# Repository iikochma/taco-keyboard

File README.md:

# Taco Keyboard

A highly ergonomic custom mechanical keyboard designed using KiCad, QMK, and Shapr3D.

The keyboard uses a single-piece design with approximately 60° tenting, integrated pointing devices for both hands, and a highly optimized keymap inspired by the Hands Down layout and Ben Vallack's 18-key keyboard concepts.

## Key Features

- 29-key custom layout ("30% keyboard")

- Approximately 60° tenting and aggressive inward rotation

- Dual integrated trackpads

- Custom reversible PCB designed in KiCad

- Custom QMK firmware

- Custom 3D-printed enclosure designed in Shapr3D

## Design Goals

The project was created to explore extreme ergonomic keyboard design while maintaining high typing efficiency.

The keymap is heavily inspired by the Hands Down layout and Ben Vallack's 18-key workflow. While the keyboard contains 29 keys, the majority of daily typing is performed using approximately 20 keys combined with layers and modifiers.

The layout was further optimized for LaTeX-heavy workflows, reducing hand movement for frequently used symbols and commands.

## Hardware

A single reversible PCB design is used for both sides of the keyboard, reducing manufacturing complexity and cost.

## Repository Structure

- `cad/` - Shapr3D, STEP, and STL files

- `firmware/` - QMK firmware

- `images/` - Photos and renders

- `pcb/` - KiCad project files

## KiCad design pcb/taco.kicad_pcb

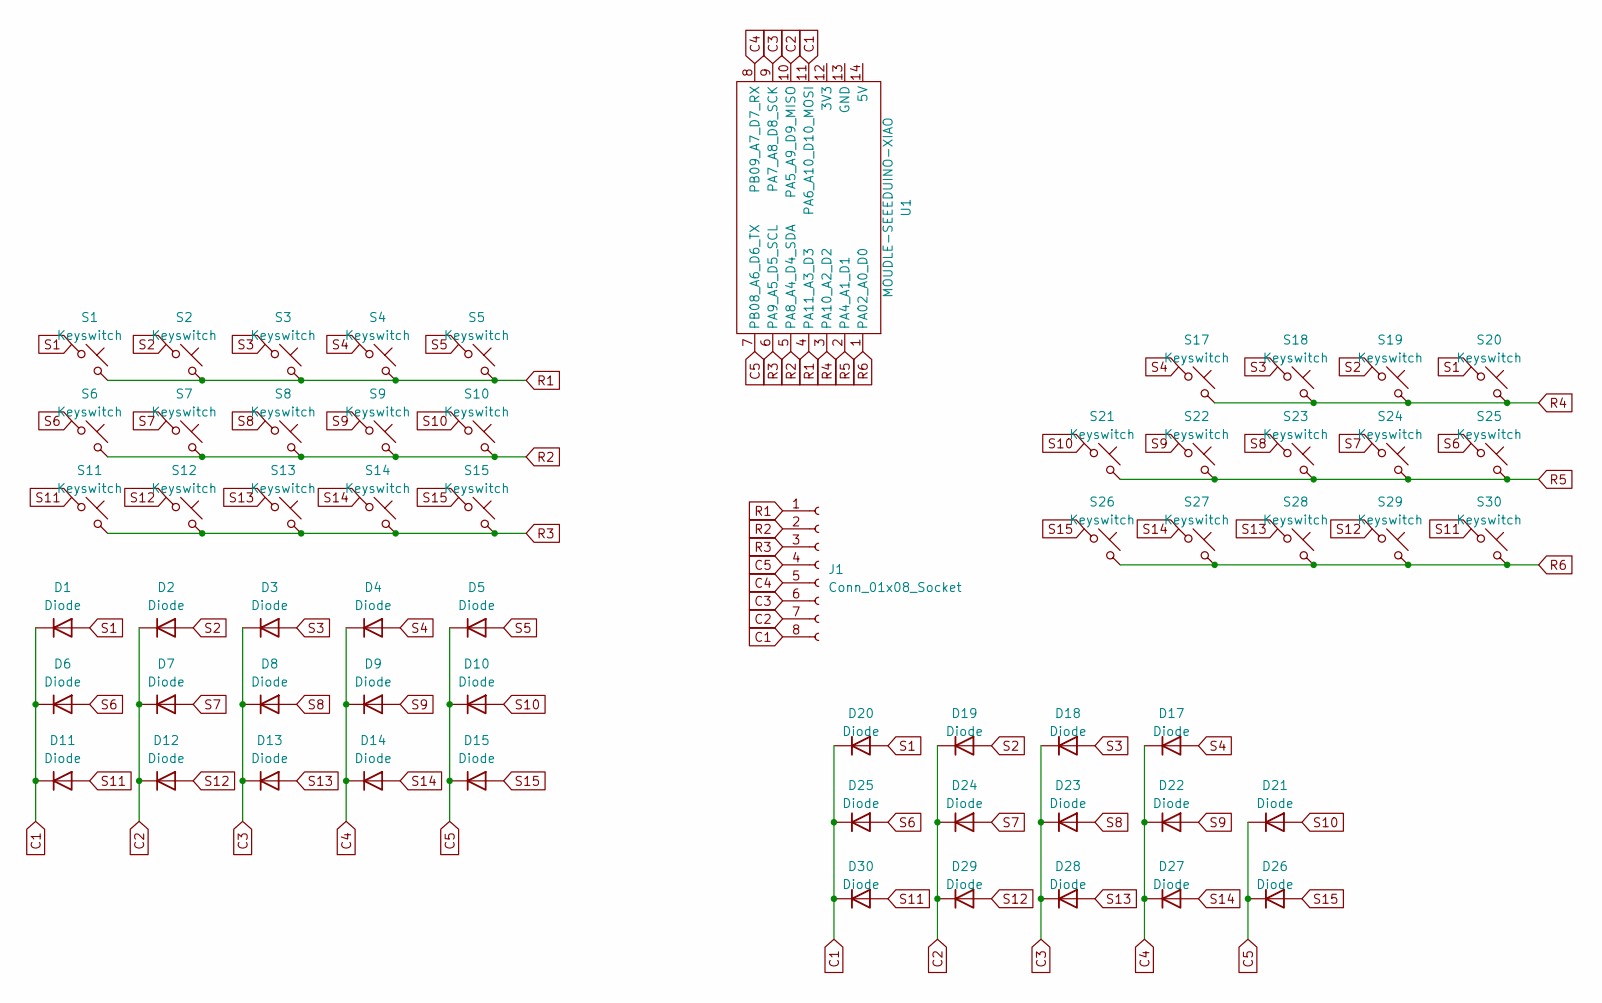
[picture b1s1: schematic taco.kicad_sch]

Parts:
D1, D2, D3, D4, D5, D6, D7, D8, D9, D10, D11, D12, D13, D14, D15, D17, D18, D19, D20, D21, D22, D23, D24, D25, D26, D27, D28, D29, D30: Diode; Diode_DO-35
J1: Conn_01x08_Socket; PinSocket_1x08_P2.54mm_Vertical
S1, S2, S3, S4, S5, S6, S7, S8, S9, S10, S11, S12, S13, S14, S15, S17, S18, S19, S20, S21, S22, S23, S24, S25, S26, S27, S28, S29, S30: Keyswitch; Choc_V1_1.00u
U1: MOUDLE-SEEEDUINO-XIAO; MOUDLE14P-2.54-21X17.8MM

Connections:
C1: D1.1 (K), D6.1 (K), D11.1 (K), D20.1 (K), D25.1 (K), D30.1 (K), J1.8, U1.11 (PA6_A10_D10_MOSI)
C2: D2.1 (K), D7.1 (K), D12.1 (K), D19.1 (K), D24.1 (K), D29.1 (K), J1.7, U1.10 (PA5_A9_D9_MISO)
C3: D3.1 (K), D8.1 (K), D13.1 (K), D18.1 (K), D23.1 (K), D28.1 (K), J1.6, U1.9 (PA7_A8_D8_SCK)
C4: D4.1 (K), D9.1 (K), D14.1 (K), D17.1 (K), D22.1 (K), D27.1 (K), J1.5, U1.8 (PB09_A7_D7_RX)
C5: D5.1 (K), D10.1 (K), D15.1 (K), D21.1 (K), D26.1 (K), J1.4, U1.7 (PB08_A6_D6_TX)
R1: J1.1, S1.2, S2.2, S3.2, S4.2, S5.2, U1.4 (PA11_A3_D3)
R2: J1.2, S6.2, S7.2, S8.2, S9.2, S10.2, U1.5 (PA8_A4_D4_SDA)
R3: J1.3, S11.2, S12.2, S13.2, S14.2, S15.2, U1.6 (PA9_A5_D5_SCL)
R4: S17.2, S18.2, S19.2, S20.2, U1.3 (PA10_A2_D2)
R5: S21.2, S22.2, S23.2, S24.2, S25.2, U1.2 (PA4_A1_D1)
R6: S26.2, S27.2, S28.2, S29.2, S30.2, U1.1 (PA02_A0_D0)
S1: D1.2 (A), D20.2 (A), S1.1, S20.1
S2: D2.2 (A), D19.2 (A), S2.1, S19.1
S3: D3.2 (A), D18.2 (A), S3.1, S18.1
S4: D4.2 (A), D17.2 (A), S4.1, S17.1
S5: D5.2 (A), S5.1
S6: D6.2 (A), D25.2 (A), S6.1, S25.1
S7: D7.2 (A), D24.2 (A), S7.1, S24.1
S8: D8.2 (A), D23.2 (A), S8.1, S23.1
S9: D9.2 (A), D22.2 (A), S9.1, S22.1
S10: D10.2 (A), D21.2 (A), S10.1, S21.1
S11: D11.2 (A), D30.2 (A), S11.1, S30.1
S12: D12.2 (A), D29.2 (A), S12.1, S29.1
S13: D13.2 (A), D28.2 (A), S13.1, S28.1
S14: D14.2 (A), D27.2 (A), S14.1, S27.1
S15: D15.2 (A), D26.2 (A), S15.1, S26.1

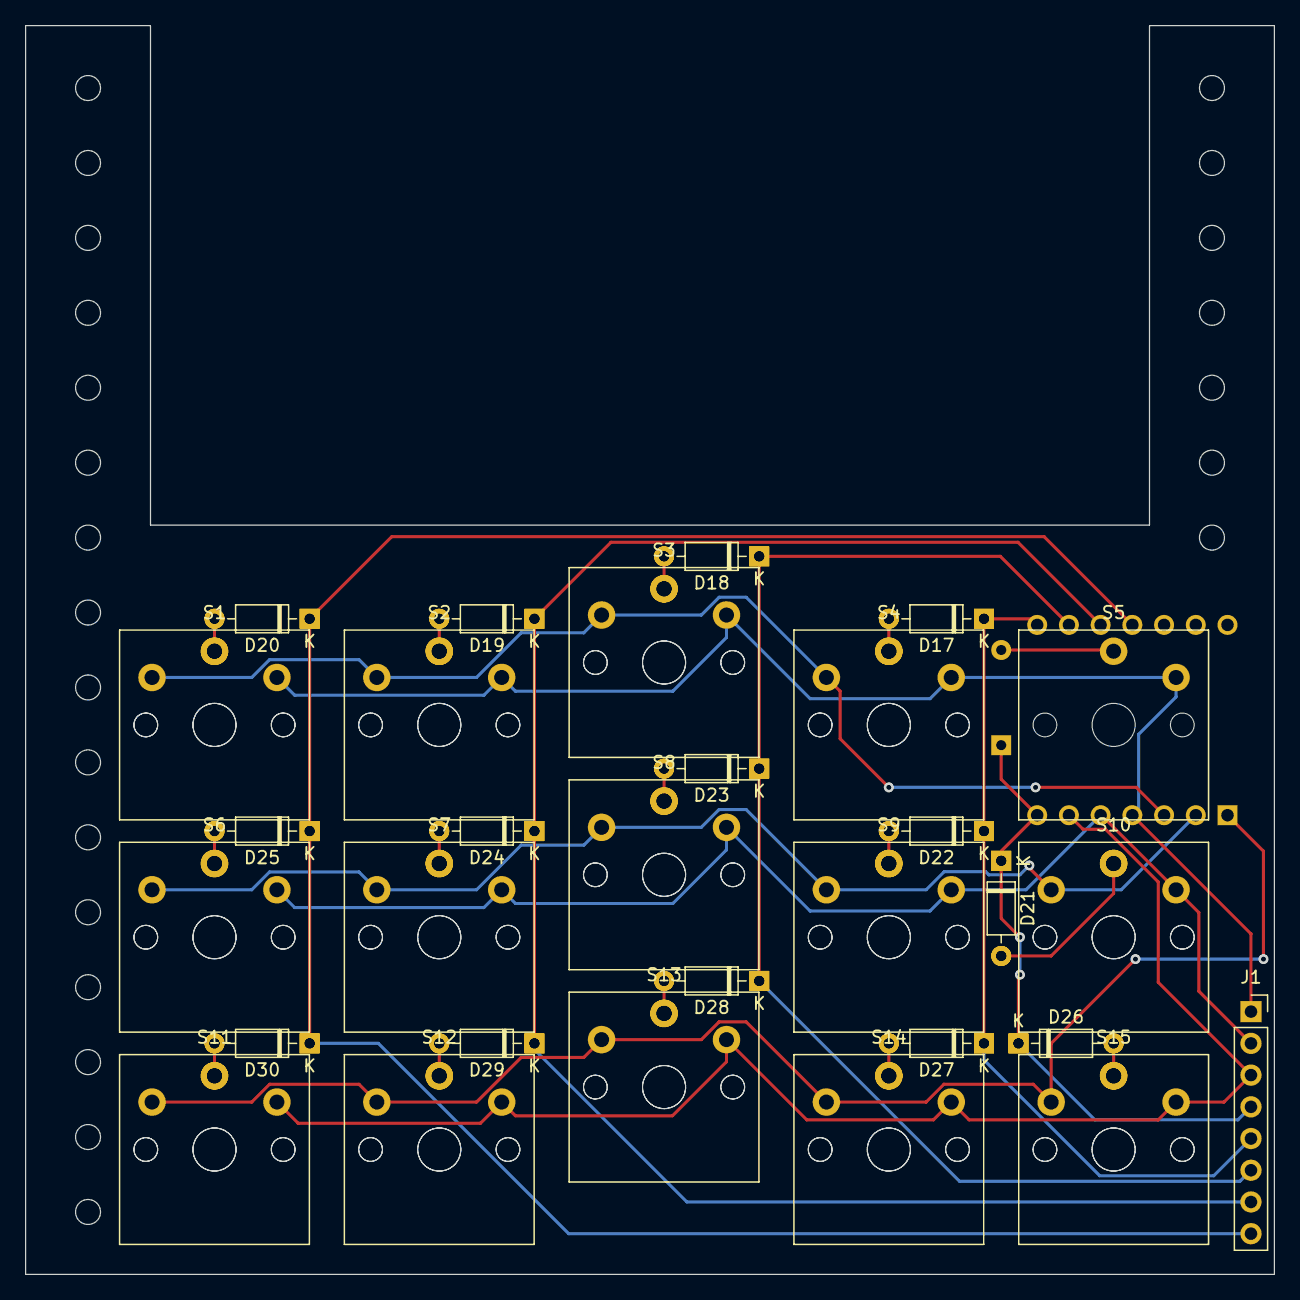
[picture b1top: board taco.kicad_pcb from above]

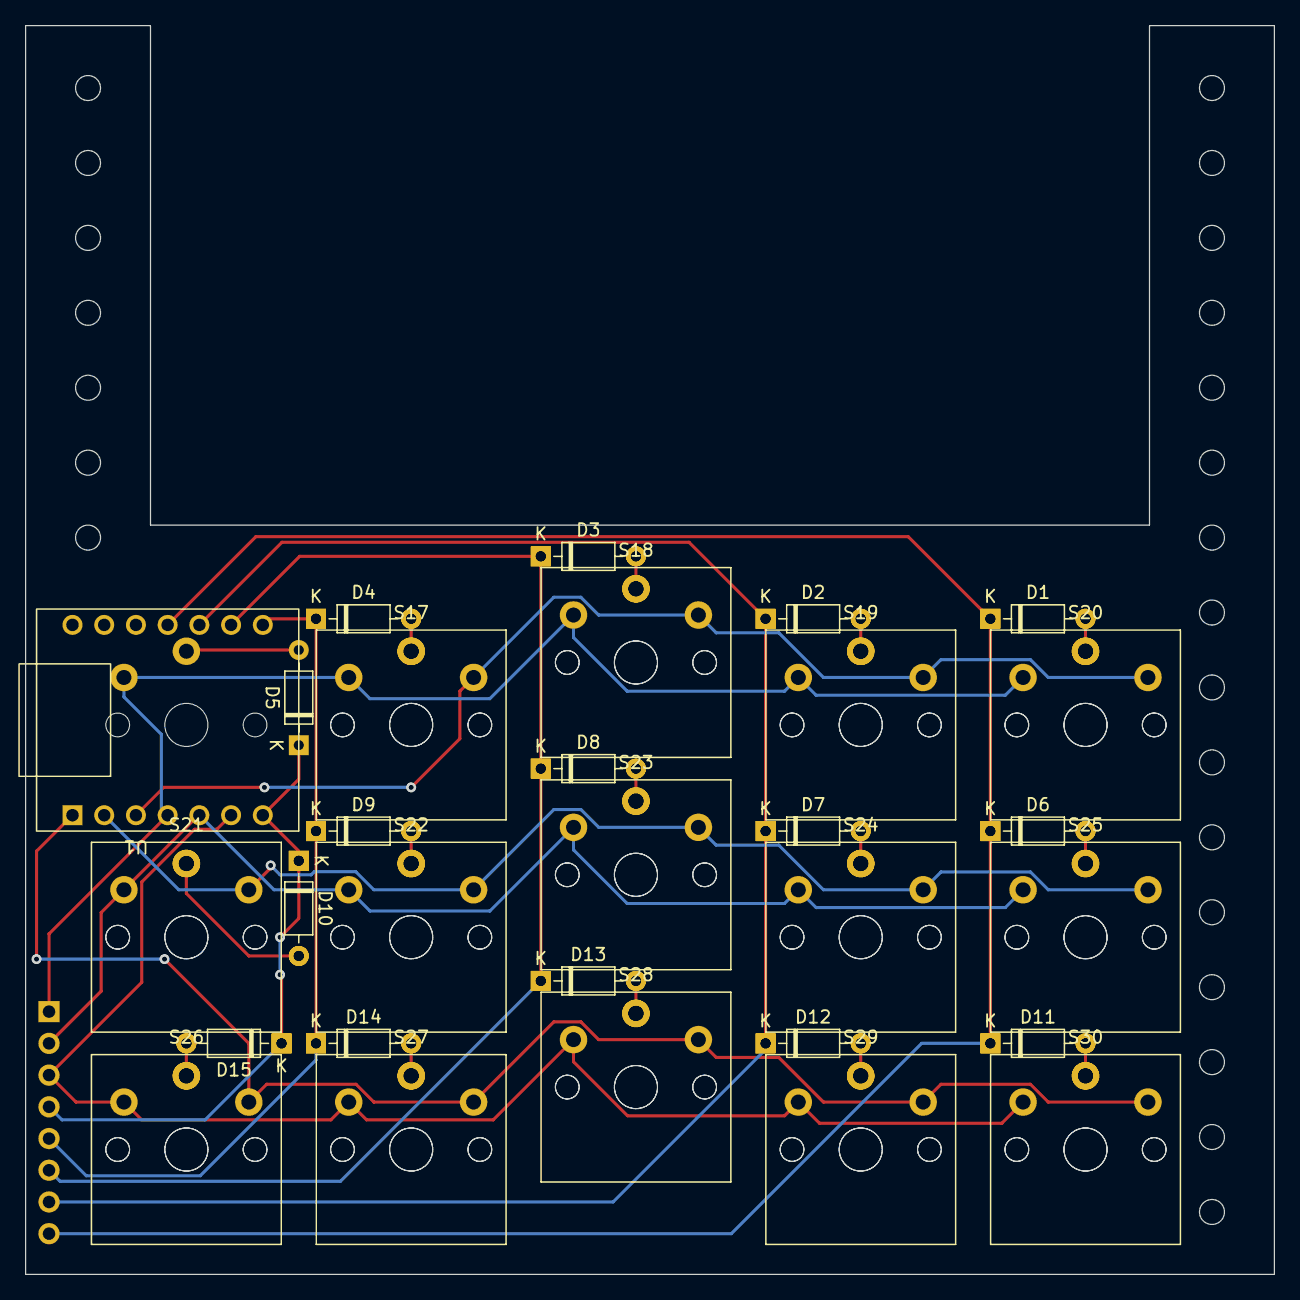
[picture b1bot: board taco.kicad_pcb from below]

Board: 2 copper layers, 100.0 x 100.0 mm, 60 parts (30 on the bottom side), 26 nets.
